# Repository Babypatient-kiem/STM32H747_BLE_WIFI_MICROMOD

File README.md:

# STM32H747_BLE_WIFI_MICROMOD
Generic module with an stm32h747 microcontroller, BLE, Bluetooth &amp; Dual-band Wifi

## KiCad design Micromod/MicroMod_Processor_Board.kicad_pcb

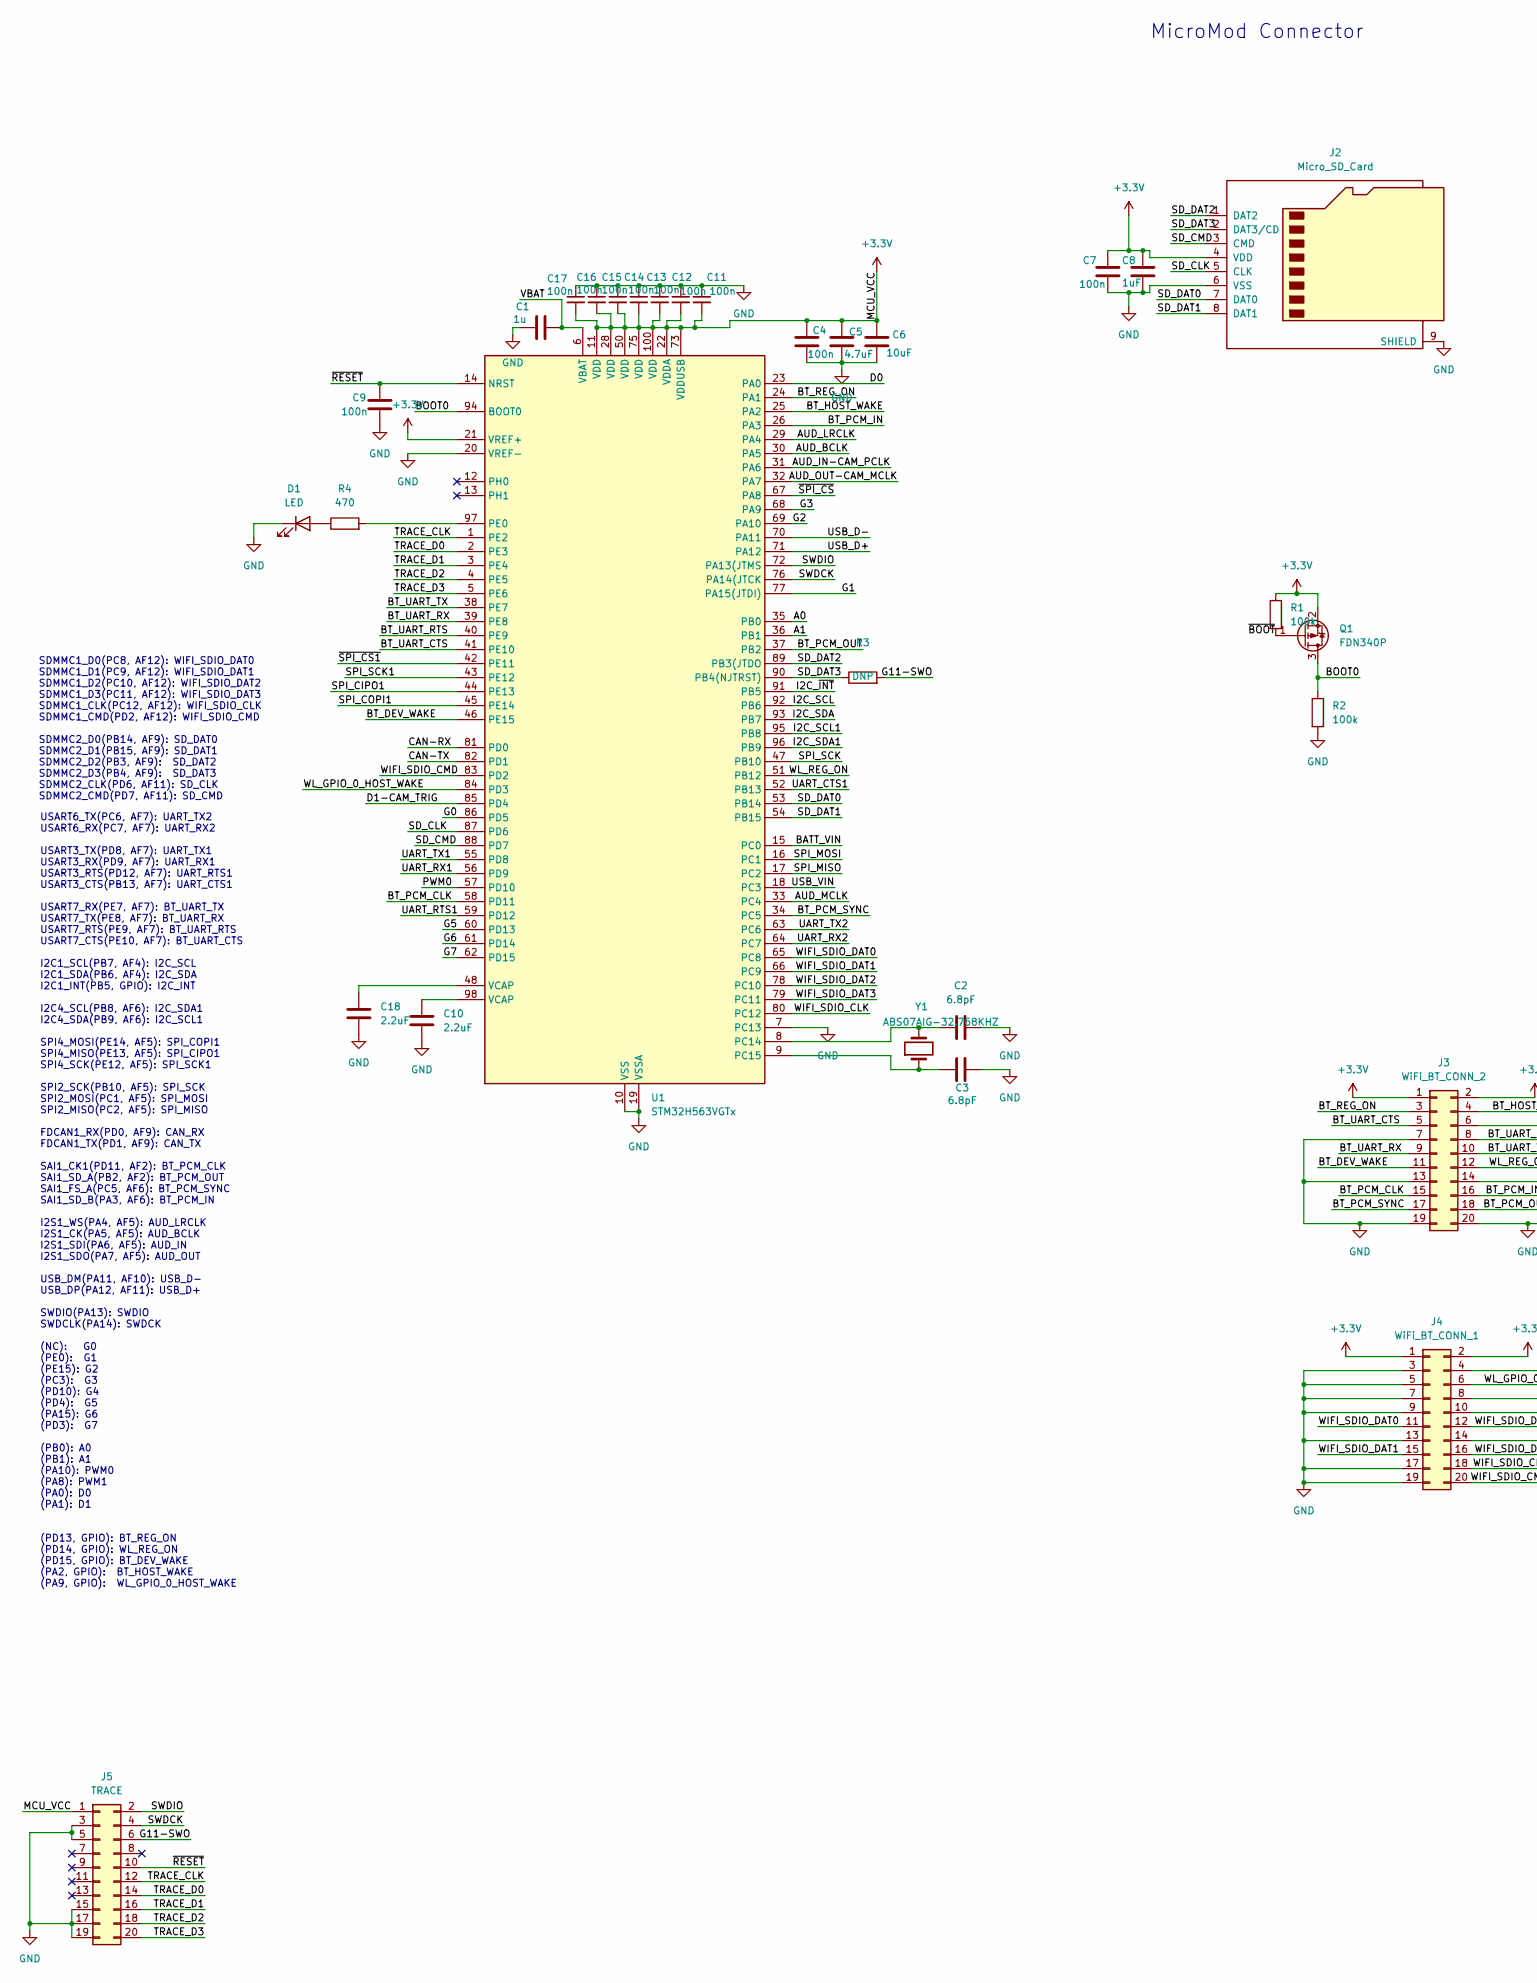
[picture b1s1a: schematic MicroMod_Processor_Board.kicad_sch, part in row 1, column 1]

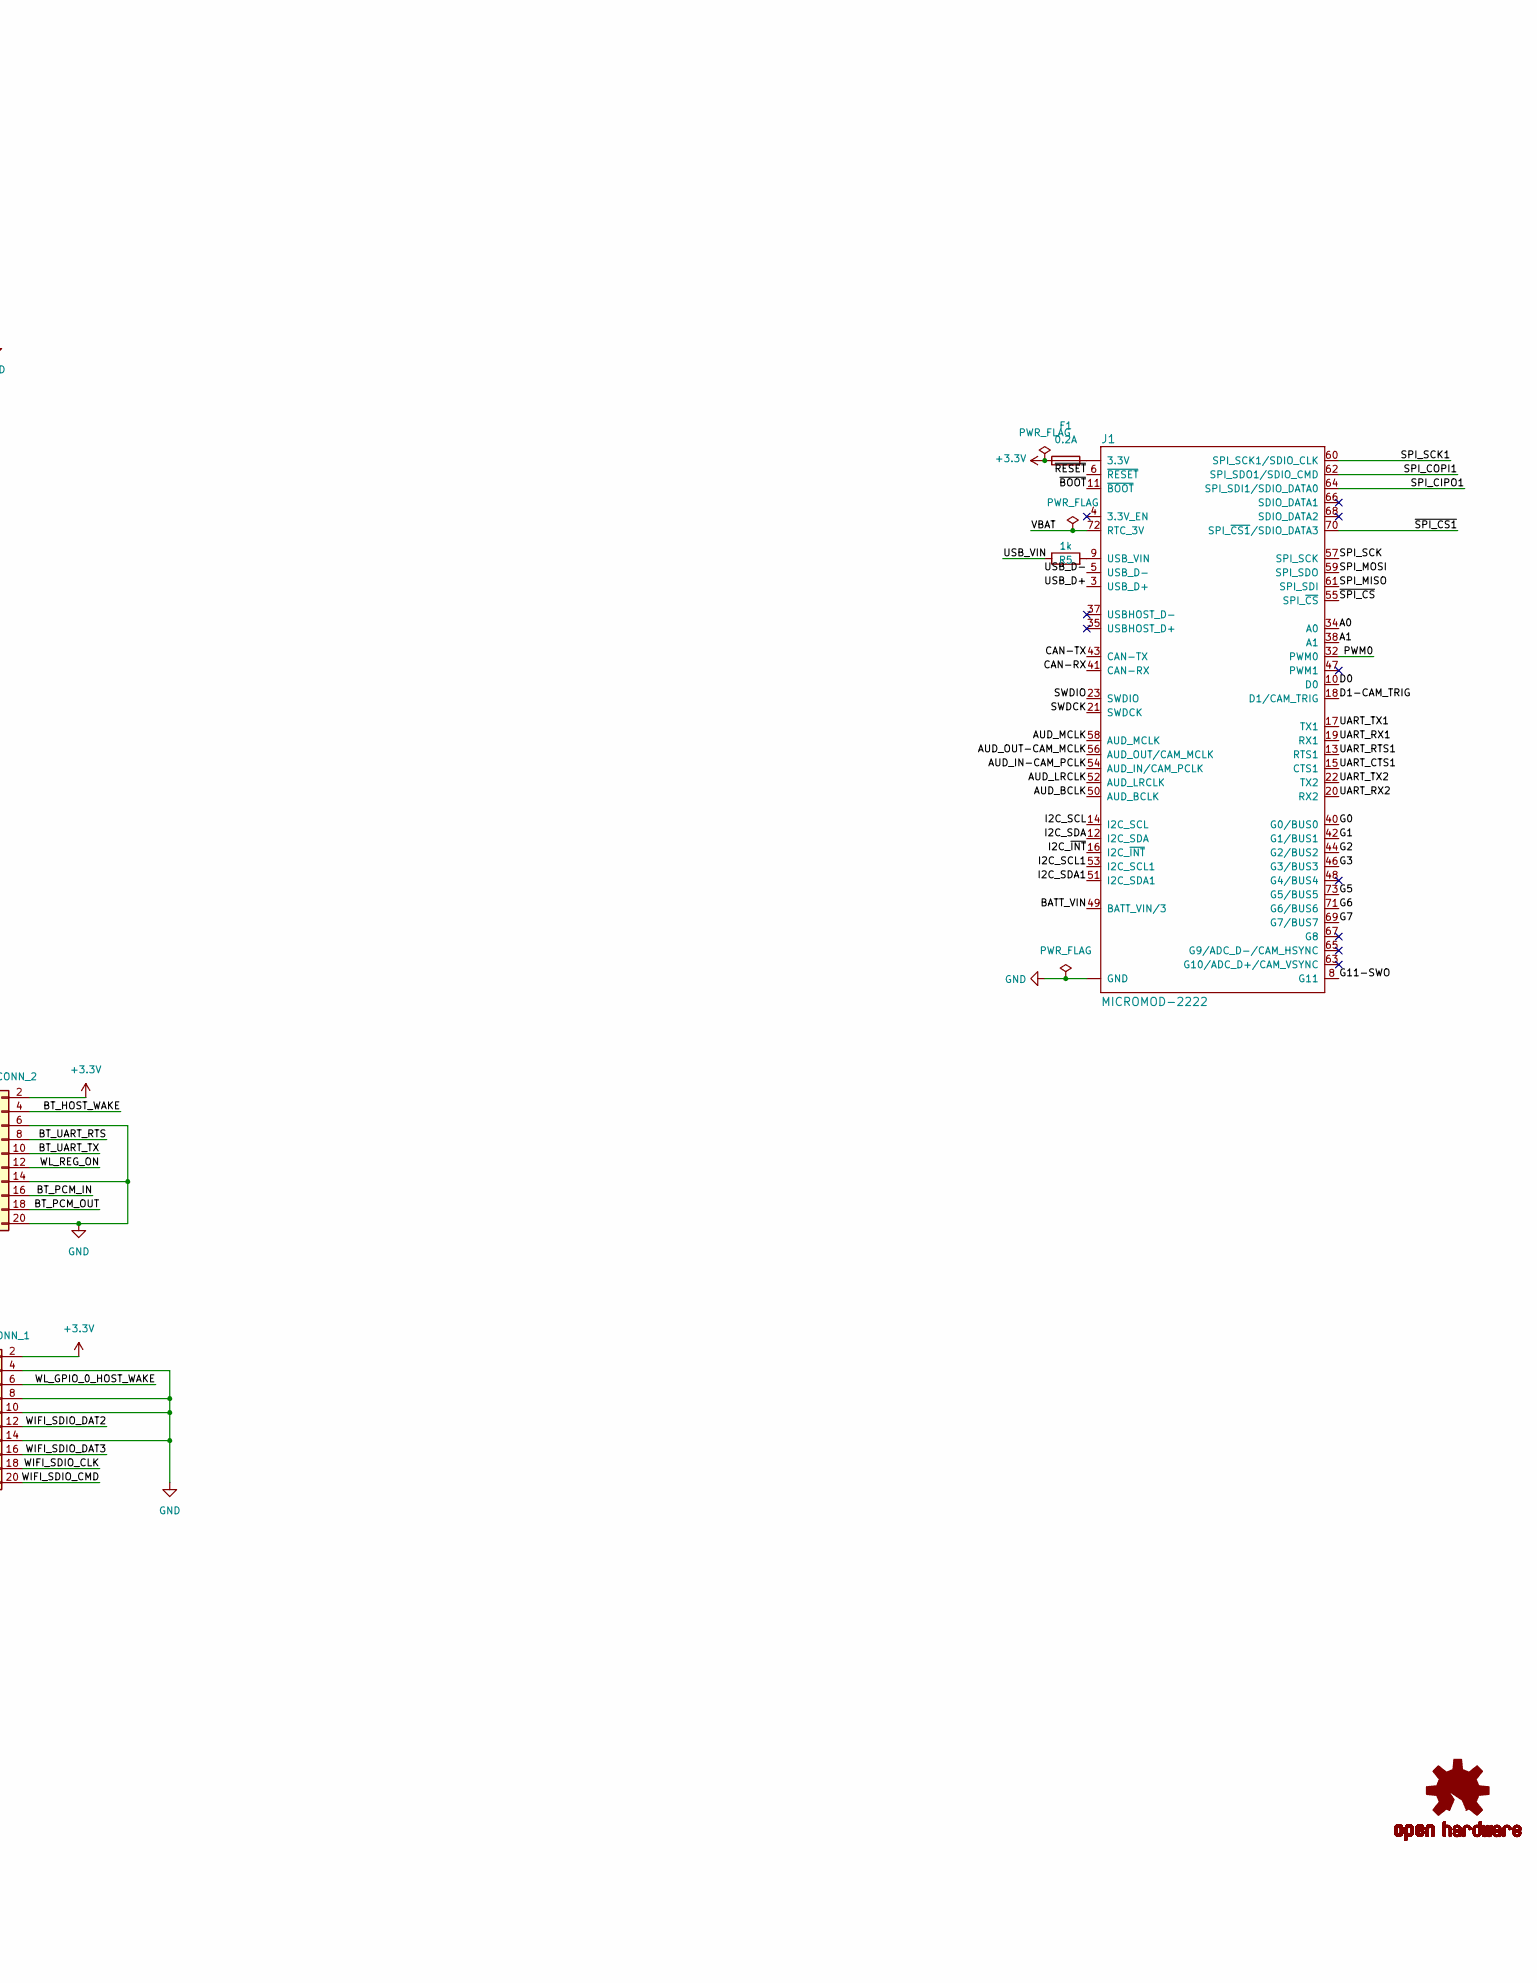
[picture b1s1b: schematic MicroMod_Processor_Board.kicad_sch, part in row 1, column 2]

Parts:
C1: 1u; C_0603_1608Metric_Pad1.08x0.95mm_HandSolder
C2, C3: 6.8pF; C_0603_1608Metric_Pad1.08x0.95mm_HandSolder
C4, C7, C9, C11, C12, C13, C14, C15, C16, C17: 100n; C_0603_1608Metric_Pad1.08x0.95mm_HandSolder
C5: 4.7uF; C_0603_1608Metric_Pad1.08x0.95mm_HandSolder
C6: 10uF; C_0603_1608Metric_Pad1.08x0.95mm_HandSolder
C8: 1uF; C_0603_1608Metric_Pad1.08x0.95mm_HandSolder
C10, C18: 2.2uF; C_0603_1608Metric_Pad1.08x0.95mm_HandSolder
D1: LED; LED_0603_1608Metric_Pad1.05x0.95mm_HandSolder
F1: 0.2A; R_0805_2012Metric_Pad1.20x1.40mm_HandSolder
J1: MICROMOD-2222; M.2-CARD-E-22
J2: Micro_SD_Card; microSD_HC_Wuerth_693072010801
J3: WiFi_BT_CONN_2; CONN20_DF40HC-25-20DS_HIR
J4: WiFi_BT_CONN_1; CONN20_DF40HC-25-20DS_HIR
J5: TRACE; PinHeader_2x10_P1.27mm_Vertical_SMD
LOGO3: OSHW-LOGOS; OSHW-LOGO-S
Q1: FDN340P; SOT-23
R1, R2: 100k; R_0603_1608Metric_Pad0.98x0.95mm_HandSolder
R3: DNP; R_0603_1608Metric_Pad0.98x0.95mm_HandSolder
R4: 470; R_0603_1608Metric_Pad0.98x0.95mm_HandSolder
R5: 1k; R_0603_1608Metric_Pad0.98x0.95mm_HandSolder
U1: STM32H563VGTx; LQFP-100_14x14mm_P0.5mm
Y1: ABS07AIG-32.768KHZ; R_1206_3216Metric_Pad1.30x1.75mm_HandSolder

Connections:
+3.3V: C4.1, C5.1, C6.1, C7.2, C8.2, C11.2, C12.2, C13.2, C14.2, C15.2, C16.2, C17.2, F1.1, J2.4 (VDD), J3.1, J3.2, J4.1, J4.2, J5.1, Q1.2 (S), R1.1, U1.11 (VDD), U1.21 (VREF+), U1.22 (VDDA), U1.28 (VDD), U1.50 (VDD), U1.73 (VDDUSB), U1.75 (VDD), U1.100 (VDD)
/A0: J1.34 (A0), U1.35 (PB0)
/A1: J1.38 (A1), U1.36 (PB1)
/AUD_BCLK: J1.50 (AUD_BCLK), U1.30 (PA5)
/AUD_IN-CAM_PCLK: J1.54 (AUD_IN/CAM_PCLK), U1.31 (PA6)
/AUD_LRCLK: J1.52 (AUD_LRCLK), U1.29 (PA4)
/AUD_MCLK: J1.58 (AUD_MCLK), U1.33 (PC4)
/AUD_OUT-CAM_MCLK: J1.56 (AUD_OUT/CAM_MCLK), U1.32 (PA7)
/BATT_VIN: J1.49 (BATT_VIN/3), U1.15 (PC0)
/BOOT0: Q1.3 (D), R2.1, U1.94 (BOOT0)
/BT_DEV_WAKE: J3.11, U1.46 (PE15)
/BT_HOST_WAKE: J3.4, U1.25 (PA2)
/BT_PCM_CLK: J3.15, U1.58 (PD11)
/BT_PCM_IN: J3.16, U1.26 (PA3)
/BT_PCM_OUT: J3.18, U1.37 (PB2)
/BT_PCM_SYNC: J3.17, U1.34 (PC5)
/BT_REG_ON: J3.3, U1.24 (PA1)
/BT_UART_CTS: J3.5, U1.41 (PE10)
/BT_UART_RTS: J3.8, U1.40 (PE9)
/BT_UART_RX: J3.9, U1.39 (PE8)
/BT_UART_TX: J3.10, U1.38 (PE7)
/CAN-RX: J1.41 (CAN-RX), U1.81 (PD0)
/CAN-TX: J1.43 (CAN-TX), U1.82 (PD1)
/D0: J1.10 (D0), U1.23 (PA0)
/D1-CAM_TRIG: J1.18 (D1/CAM_TRIG), U1.85 (PD4)
/G0: J1.40 (G0/BUS0), U1.86 (PD5)
/G1: J1.42 (G1/BUS1), U1.77 (PA15(JTDI))
/G2: J1.44 (G2/BUS2), U1.69 (PA10)
/G3: J1.46 (G3/BUS3), U1.68 (PA9)
/G5: J1.73 (G5/BUS5), U1.60 (PD13)
/G6: J1.71 (G6/BUS6), U1.61 (PD14)
/G7: J1.69 (G7/BUS7), U1.62 (PD15)
/G11-SWO: J1.8 (G11), J5.6, R3.2
/I2C_SCL: J1.14 (I2C_SCL), U1.92 (PB6)
/I2C_SCL1: J1.53 (I2C_SCL1), U1.95 (PB8)
/I2C_SDA: J1.12 (I2C_SDA), U1.93 (PB7)
/I2C_SDA1: J1.51 (I2C_SDA1), U1.96 (PB9)
/I2C_~INT: J1.16 (I2C_~INT), U1.91 (PB5)
/PWM0: J1.32 (PWM0), U1.57 (PD10)
/SD_CLK: J2.5 (CLK), U1.87 (PD6)
/SD_CMD: J2.3 (CMD), U1.88 (PD7)
/SD_DAT0: J2.7 (DAT0), U1.53 (PB14)
/SD_DAT1: J2.8 (DAT1), U1.54 (PB15)
/SD_DAT2: J2.1 (DAT2), U1.89 (PB3(JTDO)
/SD_DAT3: J2.2 (DAT3/CD), R3.1, U1.90 (PB4(NJTRST))
/SPI_CIPO1: J1.64 (SPI_SDI1/SDIO_DATA0), U1.44 (PE13)
/SPI_COPI1: J1.62 (SPI_SDO1/SDIO_CMD), U1.45 (PE14)
/SPI_MISO: J1.61 (SPI_SDI), U1.17 (PC2)
/SPI_MOSI: J1.59 (SPI_SDO), U1.16 (PC1)
/SPI_SCK: J1.57 (SPI_SCK), U1.47 (PB10)
/SPI_SCK1: J1.60 (SPI_SCK1/SDIO_CLK), U1.43 (PE12)
/SWDCK: J1.21 (SWDCK), J5.4, U1.76 (PA14(JTCK)
/SWDIO: J1.23 (SWDIO), J5.2, U1.72 (PA13(JTMS)
/TRACE_CLK: J5.12, U1.1 (PE2)
/TRACE_D0: J5.14, U1.2 (PE3)
/TRACE_D1: J5.16, U1.3 (PE4)
/TRACE_D2: J5.18, U1.4 (PE5)
/TRACE_D3: J5.20, U1.5 (PE6)
/UART_CTS1: J1.15 (CTS1), U1.52 (PB13)
/UART_RTS1: J1.13 (RTS1), U1.59 (PD12)
/UART_RX1: J1.19 (RX1), U1.56 (PD9)
/UART_RX2: J1.20 (RX2), U1.64 (PC7)
/UART_TX1: J1.17 (TX1), U1.55 (PD8)
/UART_TX2: J1.22 (TX2), U1.63 (PC6)
/USB_D+: J1.3 (USB_D+), U1.71 (PA12)
/USB_D-: J1.5 (USB_D-), U1.70 (PA11)
/USB_VIN: R5.1, U1.18 (PC3)
/VBAT: C1.1, J1.72 (RTC_3V), U1.6 (VBAT)
/WIFI_SDIO_CLK: J4.18, U1.80 (PC12)
/WIFI_SDIO_CMD: J4.20, U1.83 (PD2)
/WIFI_SDIO_DAT0: J4.11, U1.65 (PC8)
/WIFI_SDIO_DAT1: J4.15, U1.66 (PC9)
/WIFI_SDIO_DAT2: J4.12, U1.78 (PC10)
/WIFI_SDIO_DAT3: J4.16, U1.79 (PC11)
/WL_GPIO_0_HOST_WAKE: J4.6, U1.84 (PD3)
/WL_REG_ON: J3.12, U1.51 (PB12)
/~BOOT: J1.11 (~BOOT), Q1.1 (G), R1.2
/~RESET: C9.1, J1.6 (~RESET), J5.10, U1.14 (NRST)
/~SPI_CS1: J1.70 (SPI_~CS1/SDIO_DATA3), U1.42 (PE11)
/~SPI_CS: J1.55 (SPI_~CS), U1.67 (PA8)
GND: C1.2, C2.2, C3.2, C4.2, C5.2, C6.2, C7.1, C8.1, C9.2, C10.2, C11.1, C12.1, C13.1, C14.1, C15.1, C16.1, C17.1, C18.2, D1.1 (K), J1.1 (GND), J1.7 (GND), J1.33 (GND), J1.36 (GND), J1.39 (GND), J1.45 (GND), J1.75 (GND), J1.GND1 (GND), J1.GND2 (GND), J1.GND3 (GND), J2.6 (VSS), J2.9 (SHIELD), J3.6, J3.7, J3.13, J3.14, J3.19, J3.20, J4.3, J4.4, J4.5, J4.7, J4.8, J4.9, J4.10, J4.13, J4.14, J4.17, J4.19, J5.3, J5.5, J5.15, J5.17, J5.19, R2.2, U1.7 (PC13), U1.10 (VSS), U1.19 (VSSA), U1.20 (VREF-), U1.27 (VSS), U1.49 (VSS), U1.74 (VSS), U1.99 (VSS)
unnamed: C10.1, U1.98 (VCAP)
unnamed: C18.1, U1.48 (VCAP)
unnamed: D1.2 (A), R4.1
unnamed: F1.2, J1.2 (3.3V), J1.74 (3.3V)
unnamed: J1.9 (USB_VIN), R5.2
unnamed: C2.1, U1.8 (PC14), Y1.2
unnamed: C3.1, U1.9 (PC15), Y1.1
unnamed: R4.2, U1.97 (PE0)

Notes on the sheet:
MicroMod Connector
SDMMC1_D0(PC8, AF12): WIFI_SDIO_DAT0 SDMMC1_D1(PC9, AF12): WIFI_SDIO_DAT1 SDMMC1_D2(PC10, AF12): WIFI_SDIO_DAT2 SDMMC1_D3(PC11, AF12): WIFI_SDIO_DAT3 SDMMC1_CLK(PC12, AF12): WIFI_SDIO_CLK SDMMC1_CMD(PD2, AF12): WIFI_SDIO_CMD SDMMC2_D0(PB14, AF9): SD_DAT0 SDMMC2_D1(PB15, AF9): SD_DAT1 SDMMC2_D2(PB3,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
USART6_TX(PC6, AF7): UART_TX2 USART6_RX(PC7, AF7): UART_RX2 USART3_TX(PD8, AF7): UART_TX1 USART3_RX(PD9, AF7): UART_RX1 USART3_RTS(PD12, AF7): UART_RTS1 USART3_CTS(PB13, AF7): UART_CTS1 USART7_RX(PE7, AF7): BT_UART_TX USART7_TX(PE8, AF7): BT_UART_RX USART7_RTS(PE9, AF7): BT_UART_RTS USART7_CTS(PE10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

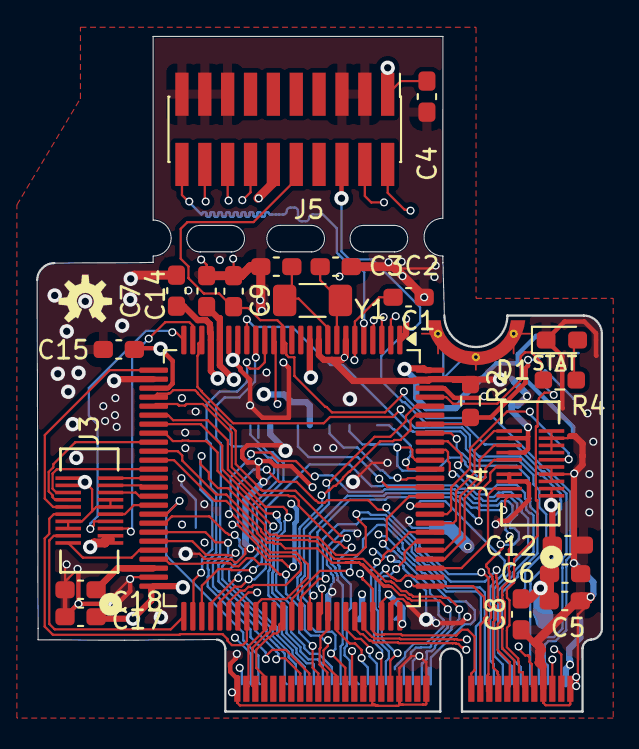
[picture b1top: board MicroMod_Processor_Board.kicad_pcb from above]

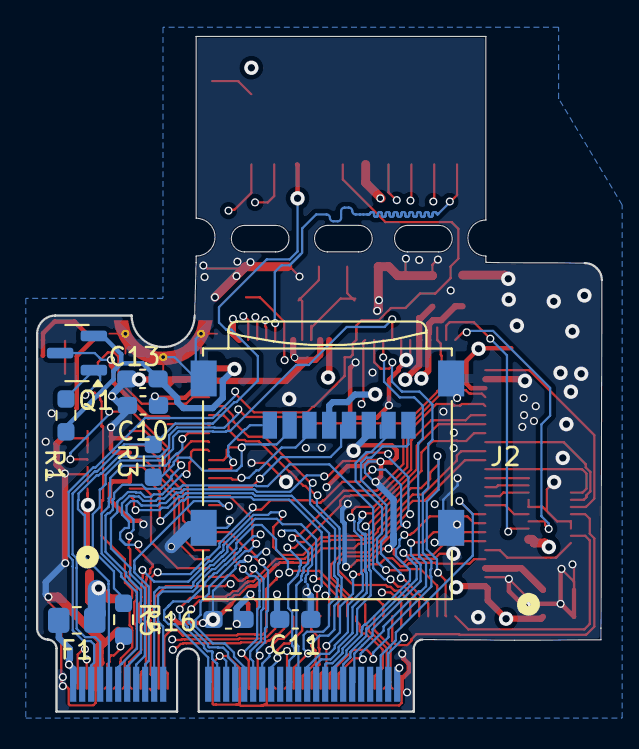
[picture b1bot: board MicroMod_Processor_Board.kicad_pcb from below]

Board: 4 copper layers, 31.4 x 37.5 mm, 36 parts (10 on the bottom side), 89 nets.

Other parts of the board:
FRAME1: FRAME-LEDGER; CREATIVE_COMMONS
LOGO1: SPECIAL_INSTRUCTIONS-ORDERING; ORDERING_INSTRUCTIONS

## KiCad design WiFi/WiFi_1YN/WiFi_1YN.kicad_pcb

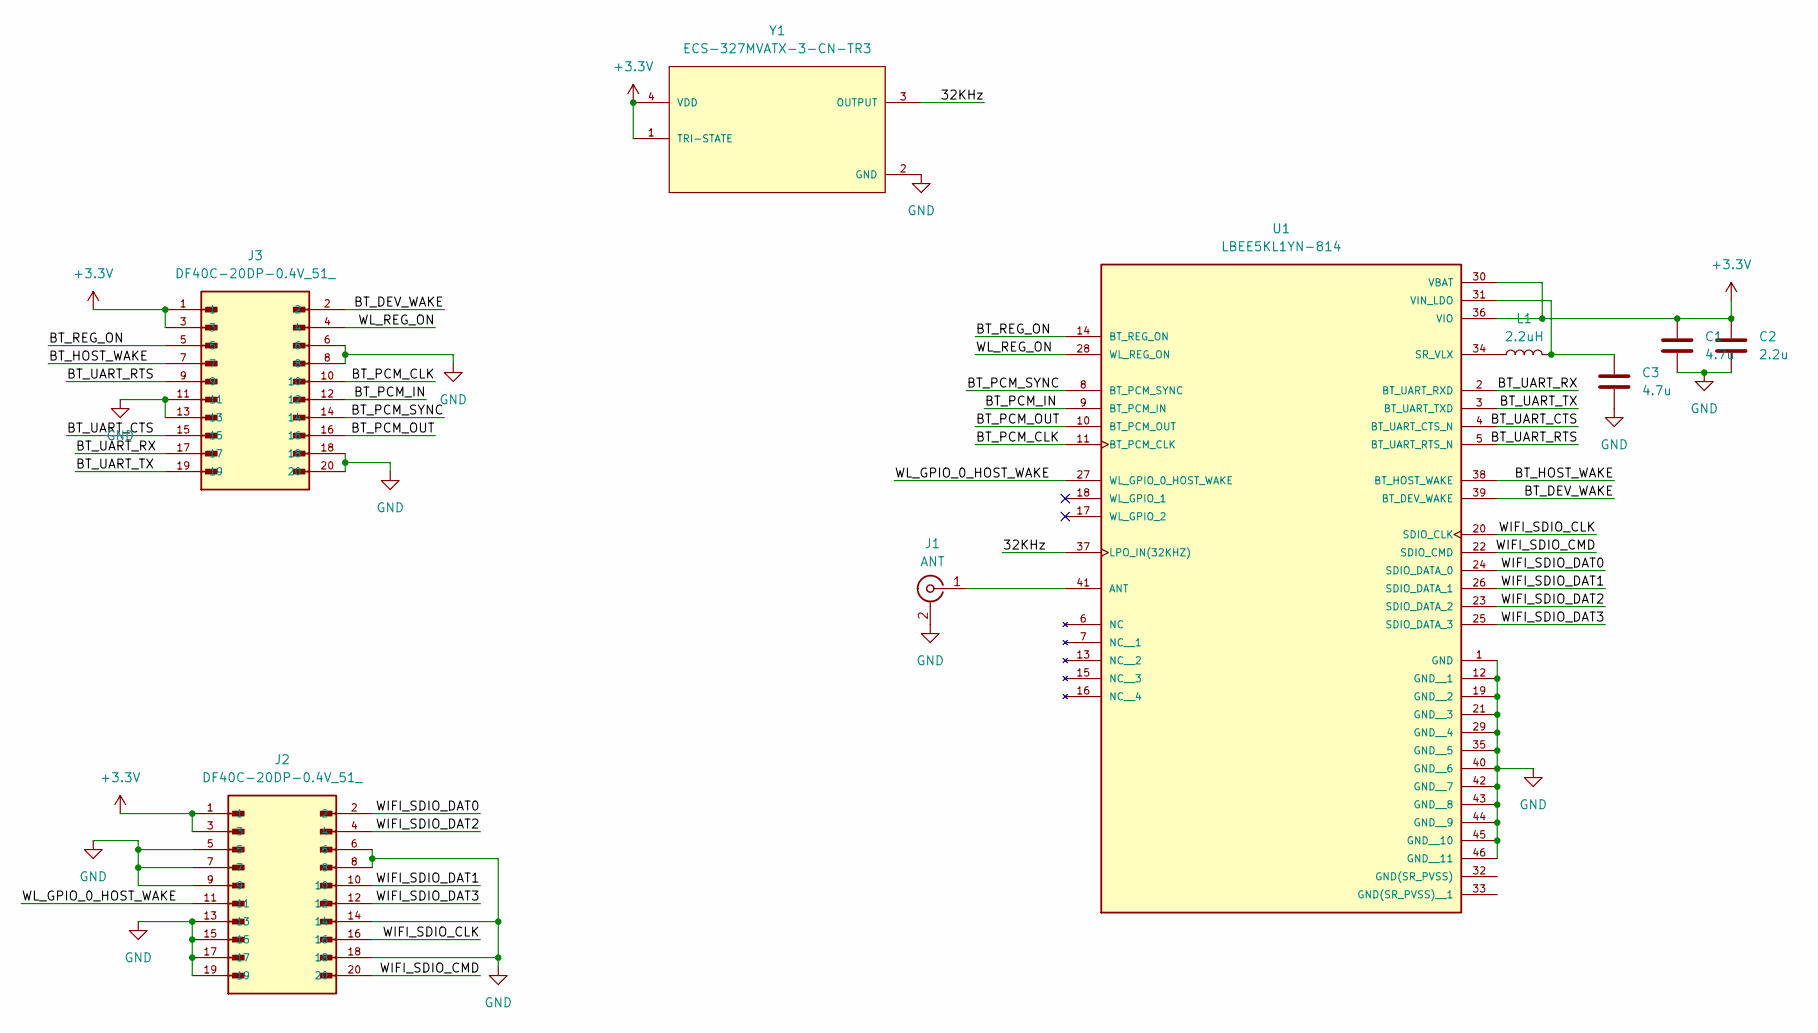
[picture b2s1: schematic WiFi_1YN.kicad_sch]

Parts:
C1, C3: 4.7u; C_0603_1608Metric_Pad1.08x0.95mm_HandSolder
C2: 2.2u; C_0603_1608Metric_Pad1.08x0.95mm_HandSolder
J1: ANT; U.FL_Molex_MCRF_73412-0110_Vertical
J2, J3: DF40C-20DP-0.4V_51_; HRS_DF40C-20DP-0.4V_51_; PARTREV 02/2020
L1: 2.2uH; L_0603_1608Metric_Pad1.05x0.95mm_HandSolder
U1: LBEE5KL1YN-814; XCVR_LBEE5KL1YN-814; PARTREV C
Y1: ECS-327MVATX-3-CN-TR3; OSC_ECS-2333-160-BN-TR; PARTREV N/A

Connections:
+3.3V: C1.1, C2.1, J2.1, J2.3, J3.1, J3.3, U1.30 (VBAT), U1.36 (VIO), Y1.1 (TRI-STATE), Y1.4 (VDD)
/32KHz: U1.37 (LPO_IN(32KHZ)), Y1.3 (OUTPUT)
/BT_DEV_WAKE: J3.2, U1.39 (BT_DEV_WAKE)
/BT_HOST_WAKE: J3.7, U1.38 (BT_HOST_WAKE)
/BT_PCM_CLK: J3.10, U1.11 (BT_PCM_CLK)
/BT_PCM_IN: J3.12, U1.9 (BT_PCM_IN)
/BT_PCM_OUT: J3.16, U1.10 (BT_PCM_OUT)
/BT_PCM_SYNC: J3.14, U1.8 (BT_PCM_SYNC)
/BT_REG_ON: J3.5, U1.14 (BT_REG_ON)
/BT_UART_CTS: J3.15, U1.4 (BT_UART_CTS_N)
/BT_UART_RTS: J3.9, U1.5 (BT_UART_RTS_N)
/BT_UART_RX: J3.17, U1.2 (BT_UART_RXD)
/BT_UART_TX: J3.19, U1.3 (BT_UART_TXD)
/WIFI_SDIO_CLK: J2.16, U1.20 (SDIO_CLK)
/WIFI_SDIO_CMD: J2.20, U1.22 (SDIO_CMD)
/WIFI_SDIO_DAT0: J2.2, U1.24 (SDIO_DATA_0)
/WIFI_SDIO_DAT1: J2.10, U1.26 (SDIO_DATA_1)
/WIFI_SDIO_DAT2: J2.4, U1.23 (SDIO_DATA_2)
/WIFI_SDIO_DAT3: J2.12, U1.25 (SDIO_DATA_3)
/WL_GPIO_0_HOST_WAKE: J2.11, U1.27 (WL_GPIO_0_HOST_WAKE)
/WL_REG_ON: J3.4, U1.28 (WL_REG_ON)
GND: C1.2, C2.2, C3.2, J1.2 (Ext), J2.5, J2.6, J2.7, J2.8, J2.9, J2.13, J2.14, J2.15, J2.17, J2.18, J2.19, J3.6, J3.8, J3.11, J3.13, J3.18, J3.20, U1.1 (GND), U1.12 (GND__1), U1.19 (GND__2), U1.21 (GND__3), U1.29 (GND__4), U1.35 (GND__5), U1.40 (GND__6), U1.42 (GND__7), U1.43 (GND__8), U1.44 (GND__9), U1.45 (GND__10), U1.46 (GND__11), Y1.2 (GND)
unnamed: J1.1 (In), U1.41 (ANT)
unnamed: L1.1, U1.34 (SR_VLX)
unnamed: C3.1, L1.2, U1.31 (VIN_LDO)

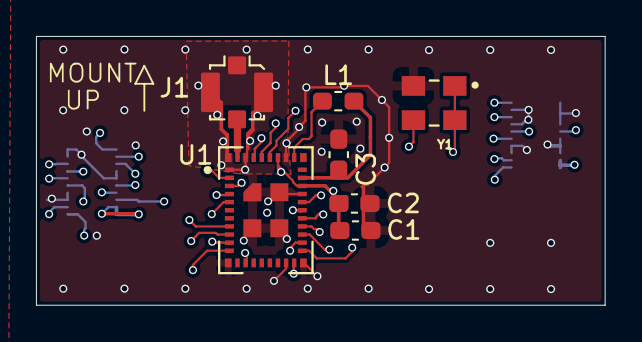
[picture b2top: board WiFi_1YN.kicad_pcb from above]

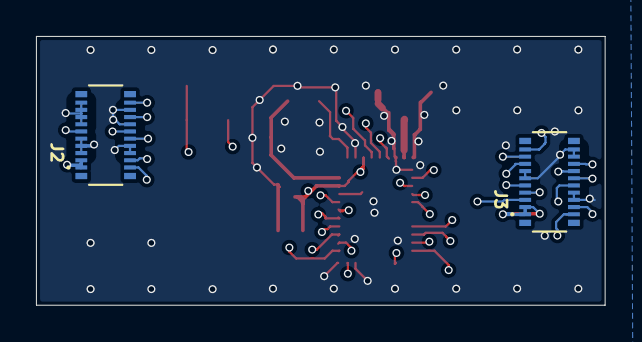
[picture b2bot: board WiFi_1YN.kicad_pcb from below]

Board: 4 copper layers, 31.6 x 14.9 mm, 9 parts (2 on the bottom side), 25 nets.

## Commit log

2025-06-03 add project skeleton
2025-06-03 add the stm32h5 with all connections to schematic
2025-06-07 progress so far
2025-06-07 almost done routing
2025-06-08 almost ready for review
2025-06-08 done
2025-06-08 add wifi module with cyw43439
2025-06-28 add some changes, make ibom from both pcbs
2025-07-04 fix the rts/cts line being swapped and missing led0 connection (PWM0)
2025-07-26 add project skeleton for new ble module using precertified module

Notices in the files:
parts and their libraries:
Released under the Creative Commons Attribution Share-Alike 4.0 License
https://creativecommons.org/licenses/by-sa/4.0
